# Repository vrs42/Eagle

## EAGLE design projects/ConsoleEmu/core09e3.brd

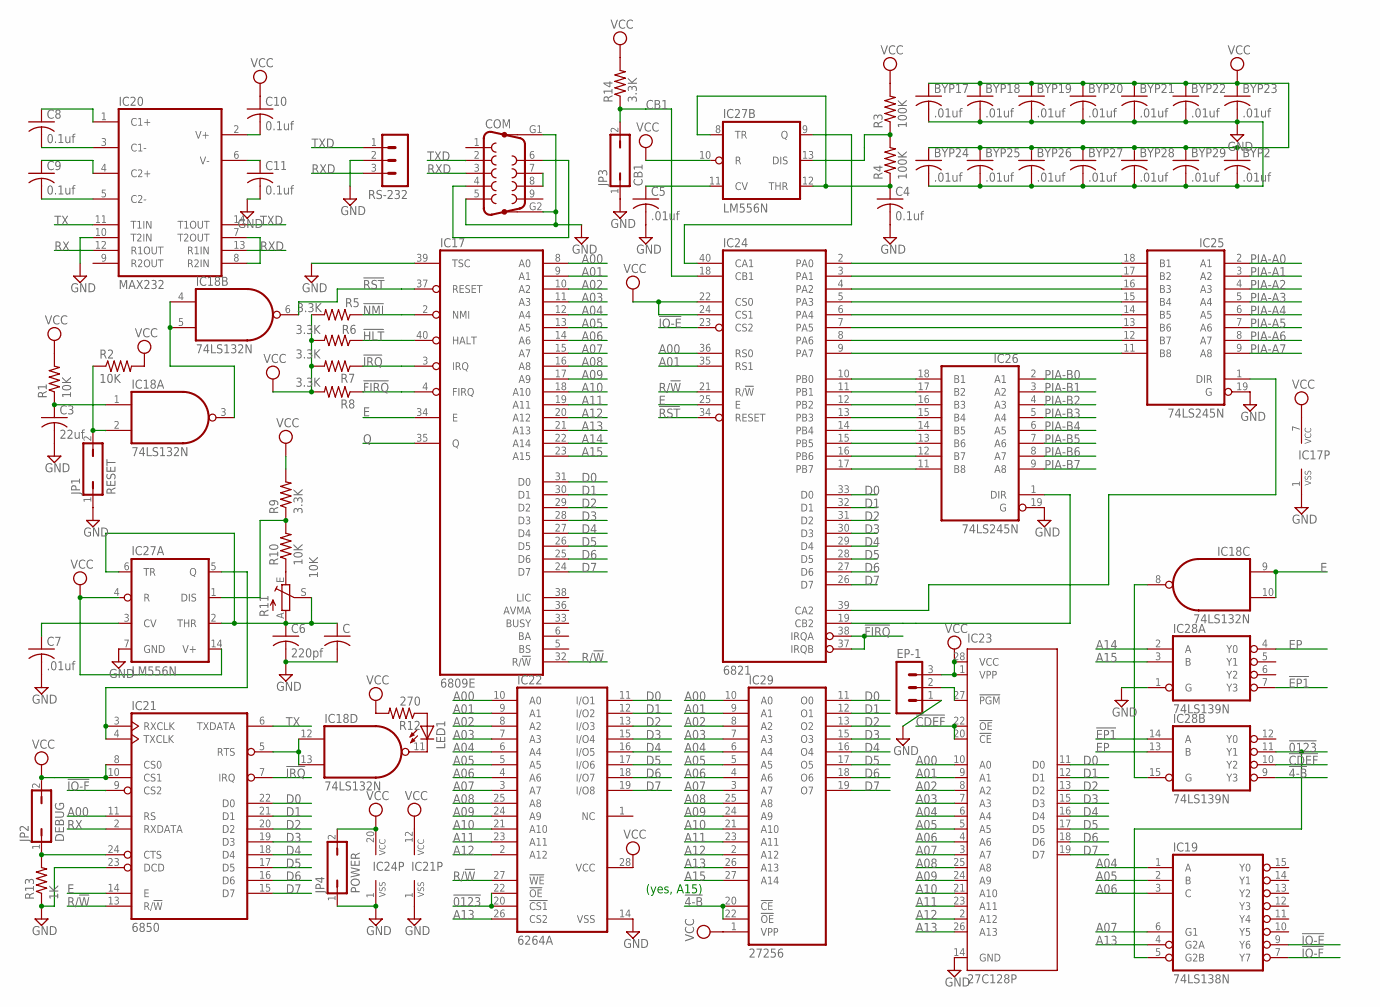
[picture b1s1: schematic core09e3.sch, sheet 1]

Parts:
BYP2, BYP17, BYP18, BYP19, BYP20, BYP21, BYP22, BYP23, BYP24, BYP25, BYP26, BYP27, BYP28, BYP29: .01uf; C050-025X075
C: C-US050-025X075; C050-025X075
C3: 22uf; C102-054X133
C4, C8, C9, C10, C11: 0.1uf; C050-025X075
C5, C7: .01uf; C050-025X075
C6: 220pf; C050-025X075
COM: F09HP
EP-1: MA03-1
IC17: 6809E; DIL40
IC18: 74LS132N; DIL14
IC19: 74LS138N; DIL16
IC20: MAX232; DIL16
IC21: 6850; DIL24
IC22: 6264A; DIL28-6
IC23: 27C128P; DIL28-6
IC24: 6821; DIL40
IC25, IC26: 74LS245N; DIL20
IC27: LM556N; DIL14
IC28: 74LS139N; DIL16
IC29: 27256; DIL28
JP1: RESET; JP1
JP2: DEBUG; JP1
JP3: CB1; JP1
JP4: POWER; JP1
LED1: LED3MM
R1, R2, R10: 10K; 0207/7
R3, R4: 100K; 0207/7
R5, R6, R7, R8, R9, R14: 3.3K; 0207/7
R11: 10K; SP19L
R12: 270; 0207/7
R13: 1K; 0207/7
RS-232: MA03-1

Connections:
!4-B: IC28.9 (Y3), IC29.20 (!CE), IC29.22 (!OE)
!0123: IC19.5 (G2B), IC22.20 (!CS1), IC22.22 (!OE), IC28.11 (Y1)
!CDEF: IC23.20 (!CE), IC23.22 (!OE), IC28.10 (Y2)
!EP1: IC28.7 (Y3), IC28.14 (A)
!FIRQ: IC17.4 (FIRQ), IC24.37 (IRQB), IC24.38 (IRQA), R8.1
!HLT: IC17.40 (HALT), R5.1
!IO-E: IC19.9 (Y6), IC24.23 (CS2)
!IO-F: IC19.7 (Y7), IC21.9 (CS2)
!IRQ: IC17.3 (IRQ), IC21.7 (IRQ), R7.1
!NMI: IC17.2 (NMI), R6.1
!RST: IC17.37 (RESET), IC18.6 (O), IC24.34 (RESET)
A00: IC17.8 (A0), IC21.11 (RS), IC22.10 (A0), IC23.10 (A0), IC24.36 (RS0), IC29.10 (A0)
A01: IC17.9 (A1), IC22.9 (A1), IC23.9 (A1), IC24.35 (RS1), IC29.9 (A1)
A02: IC17.10 (A2), IC22.8 (A2), IC23.8 (A2), IC29.8 (A2)
A03: IC17.11 (A3), IC22.7 (A3), IC23.7 (A3), IC29.7 (A3)
A04: IC17.12 (A4), IC19.1 (A), IC22.6 (A4), IC23.6 (A4), IC29.6 (A4)
A05: IC17.13 (A5), IC19.2 (B), IC22.5 (A5), IC23.5 (A5), IC29.5 (A5)
A06: IC17.14 (A6), IC19.3 (C), IC22.4 (A6), IC23.4 (A6), IC29.4 (A6)
A07: IC17.15 (A7), IC19.6 (G1), IC22.3 (A7), IC23.3 (A7), IC29.3 (A7)
A08: IC17.16 (A8), IC22.25 (A8), IC23.25 (A8), IC29.25 (A8)
A09: IC17.17 (A9), IC22.24 (A9), IC23.24 (A9), IC29.24 (A9)
A10: IC17.18 (A10), IC22.21 (A10), IC23.21 (A10), IC29.21 (A10)
A11: IC17.19 (A11), IC22.23 (A11), IC23.23 (A11), IC29.23 (A11)
A12: IC17.20 (A12), IC22.2 (A12), IC23.2 (A12), IC29.2 (A12)
A13: IC17.21 (A13), IC19.4 (G2A), IC22.26 (CS2), IC23.26 (A13), IC29.26 (A13)
A14: IC17.22 (A14), IC28.2 (A)
A15: IC17.23 (A15), IC28.3 (B), IC29.27 (A14)
CB1: IC24.18 (CB1), JP3.2, R14.1
D0: IC17.31 (D0), IC21.22 (D0), IC22.11 (I/O1), IC23.11 (D0), IC24.33 (D0), IC29.11 (O0)
D1: IC17.30 (D1), IC21.21 (D1), IC22.12 (I/O2), IC23.12 (D1), IC24.32 (D1), IC29.12 (O1)
D2: IC17.29 (D2), IC21.20 (D2), IC22.13 (I/O3), IC23.13 (D2), IC24.31 (D2), IC29.13 (O2)
D3: IC17.28 (D3), IC21.19 (D3), IC22.15 (I/O4), IC23.15 (D3), IC24.30 (D3), IC29.15 (O3)
D4: IC17.27 (D4), IC21.18 (D4), IC22.16 (I/O5), IC23.16 (D4), IC24.29 (D4), IC29.16 (O4)
D5: IC17.26 (D5), IC21.17 (D5), IC22.17 (I/O6), IC23.17 (D5), IC24.28 (D5), IC29.17 (O5)
D6: IC17.25 (D6), IC21.16 (D6), IC22.18 (I/O7), IC23.18 (D6), IC24.27 (D6), IC29.18 (O6)
D7: IC17.24 (D7), IC21.15 (D7), IC22.19 (I/O8), IC23.19 (D7), IC24.26 (D7), IC29.19 (O7)
E: IC17.34 (E), IC18.9 (I0), IC18.10 (I1), IC21.14 (E), IC24.25 (E); also elsewhere on the board
EP: IC28.4 (Y0), IC28.13 (B)
GND: BYP2.2, BYP17.2, BYP18.2, BYP19.2, BYP20.2, BYP21.2, BYP22.2, BYP23.2, BYP24.2, BYP25.2, BYP26.2, BYP27.2, BYP28.2, BYP29.2, C.2, C3.2, C4.2, C5.2, C6.2, C7.2, C11.2, COM.5, COM.G1, COM.G2, EP-1.1, IC17.1 (VSS), IC17.39 (TSC), IC18.7 (GND), IC19.8 (GND), IC20.10 (T2IN), IC20.15 (GND), IC21.1 (VSS), IC21.23 (DCD), IC22.14 (VSS), IC23.14 (GND), IC24.1 (VSS), IC25.10 (GND), IC25.19 (G), IC26.10 (GND), IC26.19 (G), IC27.7 (GND), IC28.1 (G), IC28.8 (GND), IC29.14 (GND), JP1.1, JP3.1, JP4.1, R13.1, RS-232.2; also elsewhere on the board
unnamed: COM.4, COM.6
unnamed: EP-1.2, IC23.27 (!PGM)
unnamed: IC24.2 (PA0), IC25.18 (B1)
unnamed: IC18.3 (O), IC18.4 (I0), IC18.5 (I1)
unnamed: C3.1, IC18.1 (I0), R1.1
unnamed: IC18.2 (I1), JP1.2, R2.1
unnamed: IC21.3 (RXCLK), IC21.4 (TXCLK), IC27.5 (Q)
unnamed: IC24.10 (PB0), IC26.18 (B1)
unnamed: IC24.11 (PB1), IC26.17 (B2)
unnamed: C.1, C6.1, IC27.2 (THR), IC27.6 (TR), R11.A, R11.S
unnamed: IC27.1 (DIS), R9.1, R10.2
unnamed: IC24.12 (PB2), IC26.16 (B3)
unnamed: IC24.13 (PB3), IC26.15 (B4)
unnamed: IC24.14 (PB4), IC26.14 (B5)
unnamed: IC24.15 (PB5), IC26.13 (B6)
unnamed: IC24.16 (PB6), IC26.12 (B7)
unnamed: IC24.17 (PB7), IC26.11 (B8)
unnamed: IC24.3 (PA1), IC25.17 (B2)
unnamed: IC24.4 (PA2), IC25.16 (B3)
unnamed: IC24.5 (PA3), IC25.15 (B4)
unnamed: IC24.6 (PA4), IC25.14 (B5)
unnamed: IC24.7 (PA5), IC25.13 (B6)
unnamed: IC24.8 (PA6), IC25.12 (B7)
unnamed: IC24.9 (PA7), IC25.11 (B8)
unnamed: IC24.19 (CB2), IC26.1 (DIR)
unnamed: IC24.39 (CA2), IC25.1 (DIR)
unnamed: IC24.40 (CA1), IC27.9 (Q)
unnamed: C4.1, IC27.8 (TR), IC27.12 (THR), R4.1
unnamed: IC27.13 (DIS), R3.1, R4.2
unnamed: C5.1, IC27.11 (CV)
unnamed: R10.1, R11.E
unnamed: COM.7, COM.8
unnamed: IC18.12 (I0), IC18.13 (I1), IC21.5 (RTS)
unnamed: IC18.11 (O), LED1.K (C)
unnamed: LED1.A, R12.1
unnamed: IC21.24 (CTS), JP2.1, R13.2
unnamed: IC18.8 (O), IC28.15 (G)
unnamed: IC20.7 (T2OUT), IC20.8 (R2IN)
unnamed: C7.1, IC27.3 (CV)
unnamed: C9.2, IC20.5 (C2-)
unnamed: C9.1, IC20.4 (C2+)
unnamed: C8.2, IC20.3 (C1-)
unnamed: C8.1, IC20.1 (C1+)
unnamed: C11.1, IC20.6 (V-)
unnamed: C10.2, IC20.2 (V+)
PIA-A0: IC25.2 (A1); also elsewhere on the board
PIA-A1: IC25.3 (A2); also elsewhere on the board
PIA-A2: IC25.4 (A3); also elsewhere on the board
PIA-A3: IC25.5 (A4); also elsewhere on the board
PIA-A4: IC25.6 (A5); also elsewhere on the board
PIA-A5: IC25.7 (A6); also elsewhere on the board
PIA-A6: IC25.8 (A7); also elsewhere on the board
PIA-A7: IC25.9 (A8); also elsewhere on the board
PIA-B0: IC26.2 (A1); also elsewhere on the board
PIA-B1: IC26.3 (A2); also elsewhere on the board
PIA-B2: IC26.4 (A3); also elsewhere on the board
PIA-B3: IC26.5 (A4); also elsewhere on the board
PIA-B4: IC26.6 (A5); also elsewhere on the board
PIA-B5: IC26.7 (A6); also elsewhere on the board
PIA-B6: IC26.8 (A7); also elsewhere on the board
PIA-B7: IC26.9 (A8); also elsewhere on the board
Q: IC17.35 (Q); also elsewhere on the board
R/!W: IC17.32 (R/!W), IC21.13 (R/!W), IC22.27 (!WE), IC24.21 (R/!W)
RX: IC20.12 (R1OUT), IC21.2 (RXDATA)
RXD: COM.3, IC20.13 (R1IN), RS-232.3
TX: IC20.11 (T1IN), IC21.6 (TXDATA)
TXD: COM.2, IC20.14 (T1OUT), RS-232.1
VCC: BYP2.1, BYP17.1, BYP18.1, BYP19.1, BYP20.1, BYP21.1, BYP22.1, BYP23.1, BYP24.1, BYP25.1, BYP26.1, BYP27.1, BYP28.1, BYP29.1, C10.1, EP-1.3, IC17.7 (VCC), IC18.14 (VCC), IC19.16 (VCC), IC20.16 (VCC), IC21.8 (CS0), IC21.10 (CS1), IC21.12 (VCC), IC22.28 (VCC), IC23.1 (VPP), IC23.28 (VCC), IC24.20 (VCC), IC24.22 (CS0), IC24.24 (CS1), IC25.20 (VCC), IC26.20 (VCC), IC27.4 (R), IC27.10 (R), IC27.14 (V+), IC28.16 (VCC), IC29.1 (VPP), IC29.28 (VCC), JP2.2, JP4.2, R1.2, R2.2, R3.2, R5.2, R6.2, R7.2, R8.2, R9.2, R12.2, R14.2; also elsewhere on the board

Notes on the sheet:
(yes, A15)

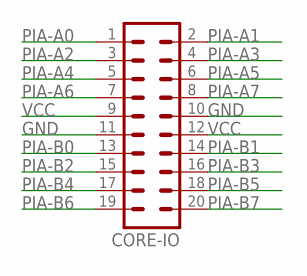
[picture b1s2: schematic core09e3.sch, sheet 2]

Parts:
CORE-IO: MA10-2

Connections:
GND: CORE-IO.10, CORE-IO.11; also elsewhere on the board
PIA-A0: CORE-IO.1; also elsewhere on the board
PIA-A1: CORE-IO.2; also elsewhere on the board
PIA-A2: CORE-IO.3; also elsewhere on the board
PIA-A3: CORE-IO.4; also elsewhere on the board
PIA-A4: CORE-IO.5; also elsewhere on the board
PIA-A5: CORE-IO.6; also elsewhere on the board
PIA-A6: CORE-IO.7; also elsewhere on the board
PIA-A7: CORE-IO.8; also elsewhere on the board
PIA-B0: CORE-IO.13; also elsewhere on the board
PIA-B1: CORE-IO.14; also elsewhere on the board
PIA-B2: CORE-IO.15; also elsewhere on the board
PIA-B3: CORE-IO.16; also elsewhere on the board
PIA-B4: CORE-IO.17; also elsewhere on the board
PIA-B5: CORE-IO.18; also elsewhere on the board
PIA-B6: CORE-IO.19; also elsewhere on the board
PIA-B7: CORE-IO.20; also elsewhere on the board
VCC: CORE-IO.9, CORE-IO.12; also elsewhere on the board

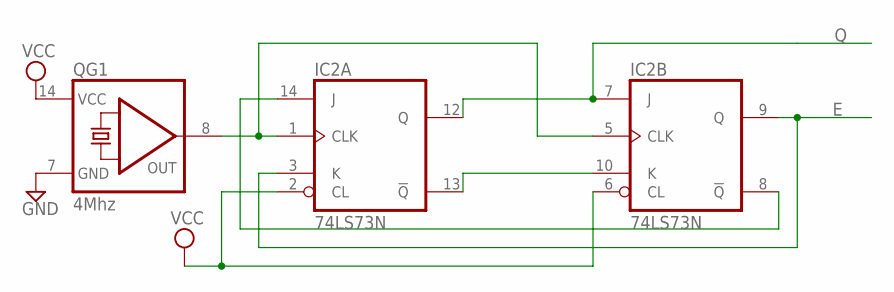
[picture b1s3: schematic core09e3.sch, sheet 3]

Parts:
IC2: 74LS73N; DIL14
QG1: 4Mhz; DIL14S

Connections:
E: IC2.3 (K), IC2.9 (Q); also elsewhere on the board
GND: IC2.11 (GND), QG1.7 (GND); also elsewhere on the board
unnamed: IC2.1 (CLK), IC2.5 (CLK), QG1.8 (OUT)
unnamed: IC2.10 (K), IC2.13 (!Q)
unnamed: IC2.8 (!Q), IC2.14 (J)
Q: IC2.7 (J), IC2.12 (Q); also elsewhere on the board
VCC: IC2.2 (CL), IC2.4 (VCC), IC2.6 (CL), QG1.14 (VCC); also elsewhere on the board

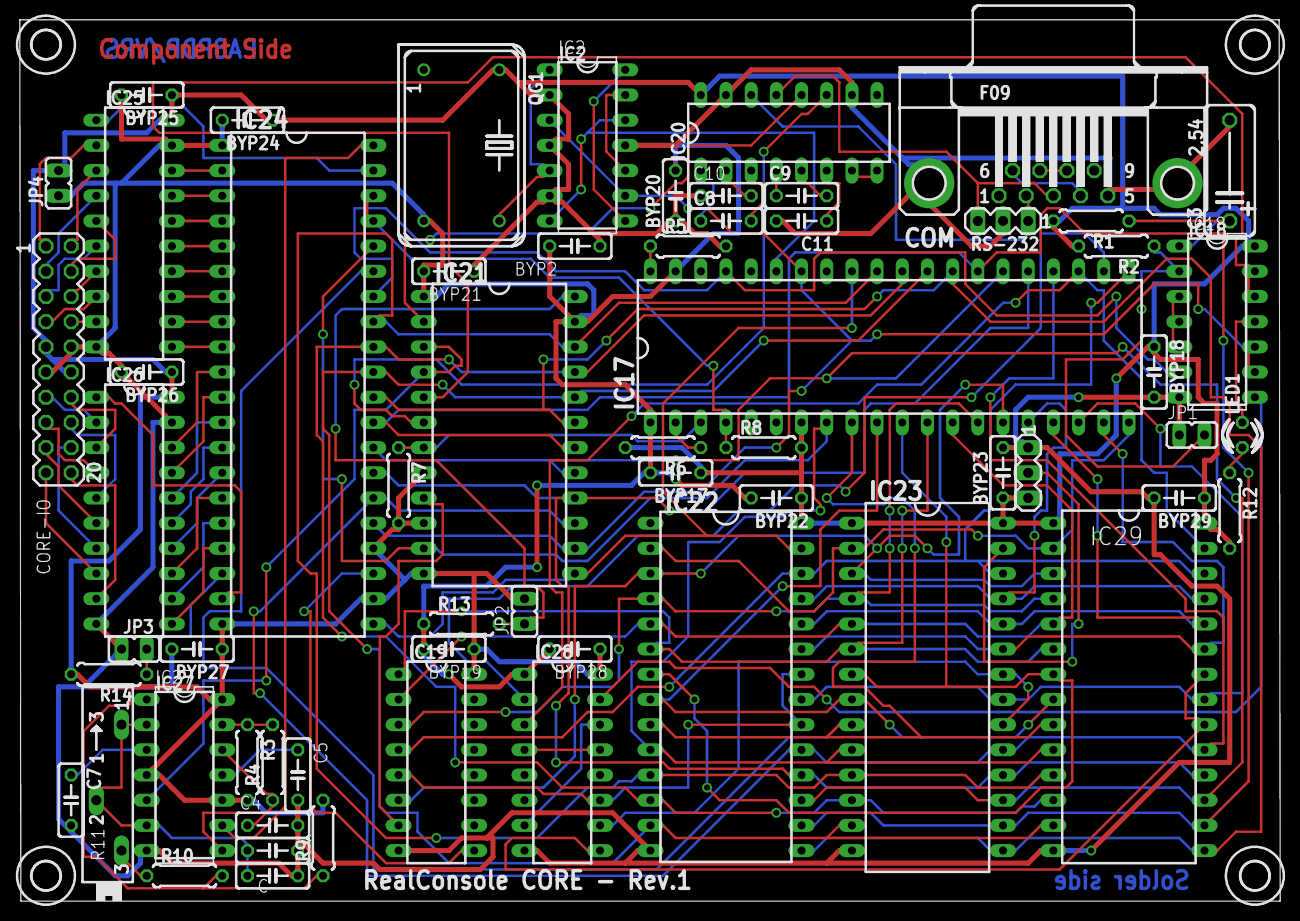
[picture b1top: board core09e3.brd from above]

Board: 2 copper layers, 127.1 x 88.9 mm, 66 parts (0 on the bottom side), 110 nets.

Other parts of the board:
U$3, U$4, U$5, U$6: 2,8

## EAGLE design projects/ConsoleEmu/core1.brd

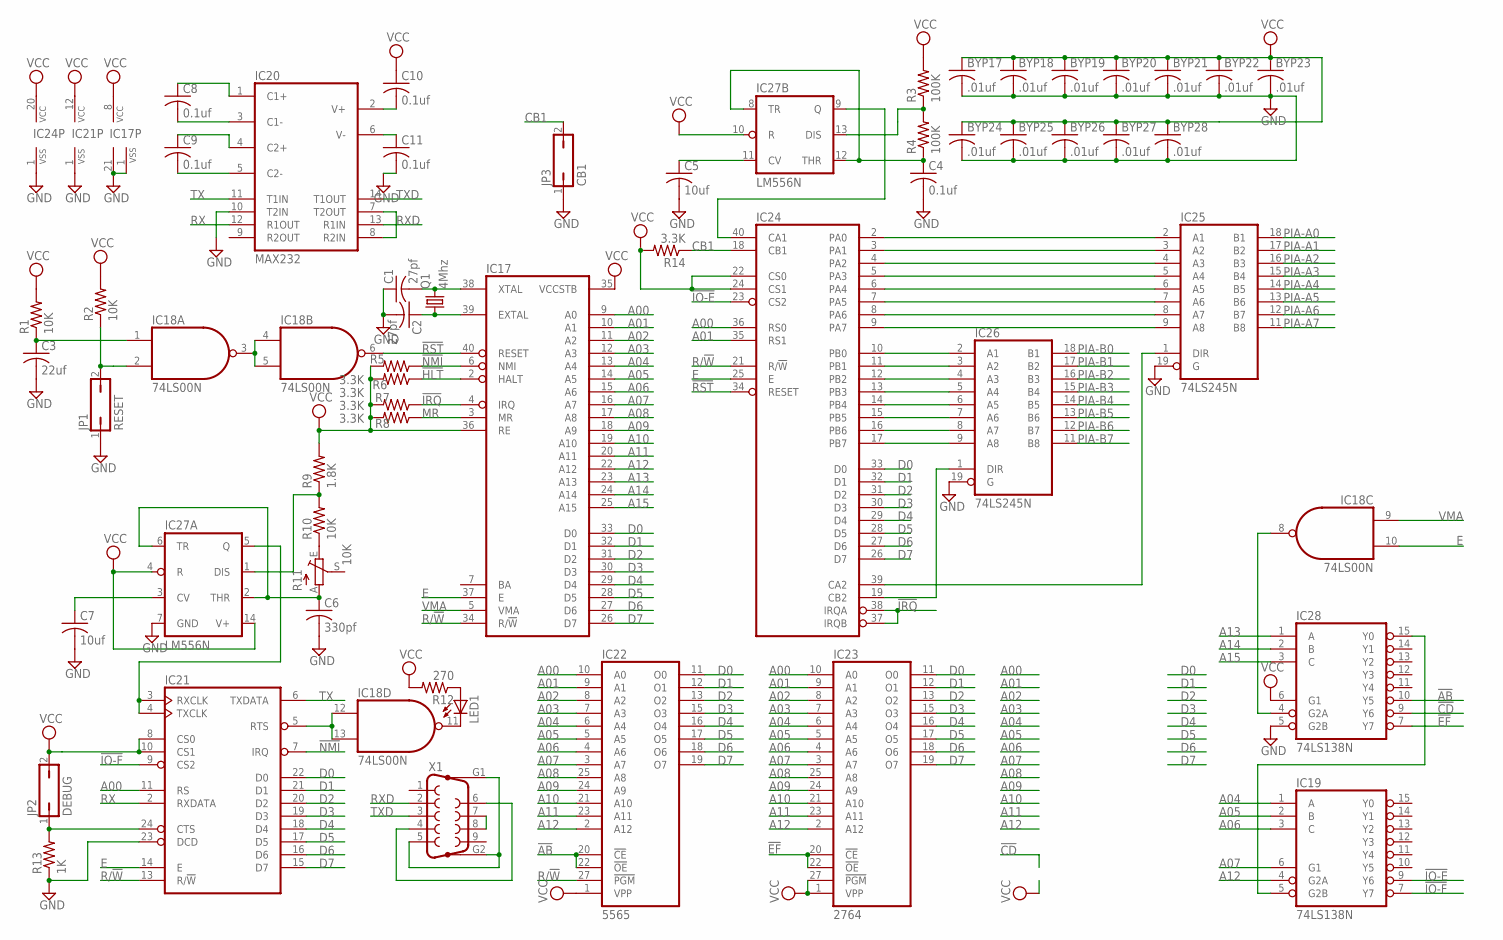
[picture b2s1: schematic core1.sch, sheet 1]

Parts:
BYP17, BYP18, BYP19, BYP20, BYP21, BYP22, BYP23, BYP24, BYP25, BYP26, BYP27, BYP28: .01uf; C050-025X075
C1, C2: 27pf; C050-025X075
C3: 22uf; C102-043X133
C4, C8, C9, C10, C11: 0.1uf; C050-025X075
C5, C7: 10uf; C050-025X075
C6: 330pf; C050-025X075
IC17: 6802; DIL40
IC18: 74LS00N; DIL14
IC19, IC28: 74LS138N; DIL16
IC20: MAX232; DIL16
IC21: 6850; DIL24
IC22: 5565; DIL28
IC23: 2764; DIL28
IC24: 6821; DIL40
IC25, IC26: 74LS245N; DIL20
IC27: LM556N; DIL14
JP1: RESET; JP1
JP2: DEBUG; JP1
JP3: CB1; JP1
LED1: LED3MM
Q1: 4Mhz; HC18U-V
R1, R2, R10: 10K; 0207/7
R3, R4: 100K; 0207/7
R5, R6, R7, R8, R14: 3.3K; 0207/7
R9: 1.8K; 0207/7
R11: 10K; SP19L
R12: 270; 0207/7
R13: 1K; 0207/7
X1: F09HP

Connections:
!AB: IC22.20 (!CE), IC22.22 (!OE), IC28.10 (Y5)
!CD: IC28.9 (Y6)
!EF: IC23.20 (!CE), IC23.22 (!OE), IC28.7 (Y7)
!HLT: IC17.2 (HALT), R5.1
!IO-E: IC19.9 (Y6), IC24.23 (CS2)
!IO-F: IC19.7 (Y7), IC21.9 (CS2)
!IRQ: IC17.4 (IRQ), IC24.37 (IRQB), IC24.38 (IRQA), R7.1
!NMI: IC17.6 (NMI), IC21.7 (IRQ), R6.1
!RST: IC17.40 (RESET), IC18.6 (O), IC24.34 (RESET)
A00: IC17.9 (A0), IC21.11 (RS), IC22.10 (A0), IC23.10 (A0), IC24.36 (RS0)
A01: IC17.10 (A1), IC22.9 (A1), IC23.9 (A1), IC24.35 (RS1)
A02: IC17.11 (A2), IC22.8 (A2), IC23.8 (A2)
A03: IC17.12 (A3), IC22.7 (A3), IC23.7 (A3)
A04: IC17.13 (A4), IC19.1 (A), IC22.6 (A4), IC23.6 (A4)
A05: IC17.14 (A5), IC19.2 (B), IC22.5 (A5), IC23.5 (A5)
A06: IC17.15 (A6), IC19.3 (C), IC22.4 (A6), IC23.4 (A6)
A07: IC17.16 (A7), IC19.6 (G1), IC22.3 (A7), IC23.3 (A7)
A08: IC17.17 (A8), IC22.25 (A8), IC23.25 (A8)
A09: IC17.18 (A9), IC22.24 (A9), IC23.24 (A9)
A10: IC17.19 (A10), IC22.21 (A10), IC23.21 (A10)
A11: IC17.20 (A11), IC22.23 (A11), IC23.23 (A11)
A12: IC17.22 (A12), IC19.4 (G2A), IC22.2 (A12), IC23.2 (A12)
A13: IC17.23 (A13), IC28.1 (A)
A14: IC17.24 (A14), IC28.2 (B)
A15: IC17.25 (A15), IC28.3 (C)
CB1: IC24.18 (CB1), JP3.2, R14.1
D0: IC17.33 (D0), IC21.22 (D0), IC22.11 (O0), IC23.11 (O0), IC24.33 (D0)
D1: IC17.32 (D1), IC21.21 (D1), IC22.12 (O1), IC23.12 (O1), IC24.32 (D1)
D2: IC17.31 (D2), IC21.20 (D2), IC22.13 (O2), IC23.13 (O2), IC24.31 (D2)
D3: IC17.30 (D3), IC21.19 (D3), IC22.15 (O3), IC23.15 (O3), IC24.30 (D3)
D4: IC17.29 (D4), IC21.18 (D4), IC22.16 (O4), IC23.16 (O4), IC24.29 (D4)
D5: IC17.28 (D5), IC21.17 (D5), IC22.17 (O5), IC23.17 (O5), IC24.28 (D5)
D6: IC17.27 (D6), IC21.16 (D6), IC22.18 (O6), IC23.18 (O6), IC24.27 (D6)
D7: IC17.26 (D7), IC21.15 (D7), IC22.19 (O7), IC23.19 (O7), IC24.26 (D7)
E: IC17.37 (E), IC18.10 (I1), IC21.14 (E), IC24.25 (E)
GND: BYP17.2, BYP18.2, BYP19.2, BYP20.2, BYP21.2, BYP22.2, BYP23.2, BYP24.2, BYP25.2, BYP26.2, BYP27.2, BYP28.2, C1.1, C2.2, C3.2, C4.2, C5.2, C6.2, C7.2, C11.2, IC17.1 (VSS), IC17.21 (VSS), IC18.7 (GND), IC19.8 (GND), IC20.10 (T2IN), IC20.15 (GND), IC21.1 (VSS), IC21.23 (DCD), IC22.14 (GND), IC23.14 (GND), IC24.1 (VSS), IC25.10 (GND), IC25.19 (G), IC26.10 (GND), IC26.19 (G), IC27.7 (GND), IC28.5 (G2B), IC28.8 (GND), JP1.1, JP3.1, R13.1; also elsewhere on the board
MR: IC17.3 (MR), R8.1
unnamed: C2.1, IC17.39 (EXTAL), Q1.1
unnamed: C1.2, IC17.38 (XTAL), Q1.2
unnamed: IC24.2 (PA0), IC25.2 (A1)
unnamed: IC18.3 (O), IC18.4 (I0), IC18.5 (I1)
unnamed: C3.1, IC18.1 (I0), R1.1
unnamed: IC18.2 (I1), JP1.2, R2.1
unnamed: IC21.3 (RXCLK), IC21.4 (TXCLK), IC27.5 (Q)
unnamed: IC24.10 (PB0), IC26.2 (A1)
unnamed: IC24.11 (PB1), IC26.3 (A2)
unnamed: C6.1, IC27.2 (THR), IC27.6 (TR), R11.A
unnamed: IC27.1 (DIS), R9.1, R10.2
unnamed: IC24.12 (PB2), IC26.4 (A3)
unnamed: IC24.13 (PB3), IC26.5 (A4)
unnamed: IC24.14 (PB4), IC26.6 (A5)
unnamed: IC24.15 (PB5), IC26.7 (A6)
unnamed: IC24.16 (PB6), IC26.8 (A7)
unnamed: IC24.17 (PB7), IC26.9 (A8)
unnamed: IC24.3 (PA1), IC25.3 (A2)
unnamed: IC24.4 (PA2), IC25.4 (A3)
unnamed: IC24.5 (PA3), IC25.5 (A4)
unnamed: IC24.6 (PA4), IC25.6 (A5)
unnamed: IC24.7 (PA5), IC25.7 (A6)
unnamed: IC24.8 (PA6), IC25.8 (A7)
unnamed: IC24.9 (PA7), IC25.9 (A8)
unnamed: IC24.19 (CB2), IC26.1 (DIR)
unnamed: IC24.39 (CA2), IC25.1 (DIR)
unnamed: IC24.40 (CA1), IC27.9 (Q)
unnamed: C4.1, IC27.8 (TR), IC27.12 (THR), R4.1
unnamed: IC27.13 (DIS), R3.1, R4.2
unnamed: C5.1, IC27.11 (CV)
unnamed: R10.1, R11.E
unnamed: X1.4, X1.6
unnamed: X1.7, X1.8
unnamed: X1.5, X1.G1, X1.G2
unnamed: IC18.12 (I0), IC18.13 (I1), IC21.5 (RTS)
unnamed: IC18.11 (O), LED1.K (C)
unnamed: LED1.A, R12.1
unnamed: IC21.24 (CTS), JP2.1, R13.2
unnamed: IC18.8 (O), IC28.4 (G2A)
unnamed: IC19.5 (G2B), IC28.15 (Y0)
unnamed: IC20.7 (T2OUT), IC20.8 (R2IN)
unnamed: C7.1, IC27.3 (CV)
unnamed: C9.2, IC20.5 (C2-)
unnamed: C9.1, IC20.4 (C2+)
unnamed: C8.2, IC20.3 (C1-)
unnamed: C8.1, IC20.1 (C1+)
unnamed: C11.1, IC20.6 (V-)
unnamed: C10.2, IC20.2 (V+)
PIA-A0: IC25.18 (B1); also elsewhere on the board
PIA-A1: IC25.17 (B2); also elsewhere on the board
PIA-A2: IC25.16 (B3); also elsewhere on the board
PIA-A3: IC25.15 (B4); also elsewhere on the board
PIA-A4: IC25.14 (B5); also elsewhere on the board
PIA-A5: IC25.13 (B6); also elsewhere on the board
PIA-A6: IC25.12 (B7); also elsewhere on the board
PIA-A7: IC25.11 (B8); also elsewhere on the board
PIA-B0: IC26.18 (B1); also elsewhere on the board
PIA-B1: IC26.17 (B2); also elsewhere on the board
PIA-B2: IC26.16 (B3); also elsewhere on the board
PIA-B3: IC26.15 (B4); also elsewhere on the board
PIA-B4: IC26.14 (B5); also elsewhere on the board
PIA-B5: IC26.13 (B6); also elsewhere on the board
PIA-B6: IC26.12 (B7); also elsewhere on the board
PIA-B7: IC26.11 (B8); also elsewhere on the board
R/!W: IC17.34 (R/!W), IC21.13 (R/!W), IC22.27 (!PGM), IC24.21 (R/!W)
RX: IC20.12 (R1OUT), IC21.2 (RXDATA)
RXD: IC20.13 (R1IN), X1.2
TX: IC20.11 (T1IN), IC21.6 (TXDATA)
TXD: IC20.14 (T1OUT), X1.3
VCC: BYP17.1, BYP18.1, BYP19.1, BYP20.1, BYP21.1, BYP22.1, BYP23.1, BYP24.1, BYP25.1, BYP26.1, BYP27.1, BYP28.1, C10.1, IC17.8 (VCC), IC17.35 (VCCSTB), IC17.36 (RE), IC18.14 (VCC), IC19.16 (VCC), IC20.16 (VCC), IC21.8 (CS0), IC21.10 (CS1), IC21.12 (VCC), IC22.1 (VPP), IC22.28 (VCC), IC23.1 (VPP), IC23.27 (!PGM), IC23.28 (VCC), IC24.20 (VCC), IC24.22 (CS0), IC24.24 (CS1), IC25.20 (VCC), IC26.20 (VCC), IC27.4 (R), IC27.10 (R), IC27.14 (V+), IC28.6 (G1), IC28.16 (VCC), JP2.2, R1.2, R2.2, R3.2, R5.2, R6.2, R7.2, R8.2, R9.2, R12.2, R14.2; also elsewhere on the board
VMA: IC17.5 (VMA), IC18.9 (I0)

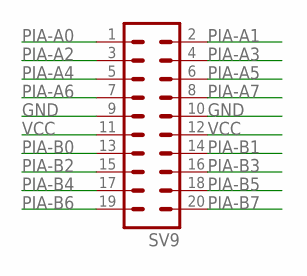
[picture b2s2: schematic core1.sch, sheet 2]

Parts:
SV9: MA10-2

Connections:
GND: SV9.9, SV9.10; also elsewhere on the board
PIA-A0: SV9.1; also elsewhere on the board
PIA-A1: SV9.2; also elsewhere on the board
PIA-A2: SV9.3; also elsewhere on the board
PIA-A3: SV9.4; also elsewhere on the board
PIA-A4: SV9.5; also elsewhere on the board
PIA-A5: SV9.6; also elsewhere on the board
PIA-A6: SV9.7; also elsewhere on the board
PIA-A7: SV9.8; also elsewhere on the board
PIA-B0: SV9.13; also elsewhere on the board
PIA-B1: SV9.14; also elsewhere on the board
PIA-B2: SV9.15; also elsewhere on the board
PIA-B3: SV9.16; also elsewhere on the board
PIA-B4: SV9.17; also elsewhere on the board
PIA-B5: SV9.18; also elsewhere on the board
PIA-B6: SV9.19; also elsewhere on the board
PIA-B7: SV9.20; also elsewhere on the board
VCC: SV9.11, SV9.12; also elsewhere on the board

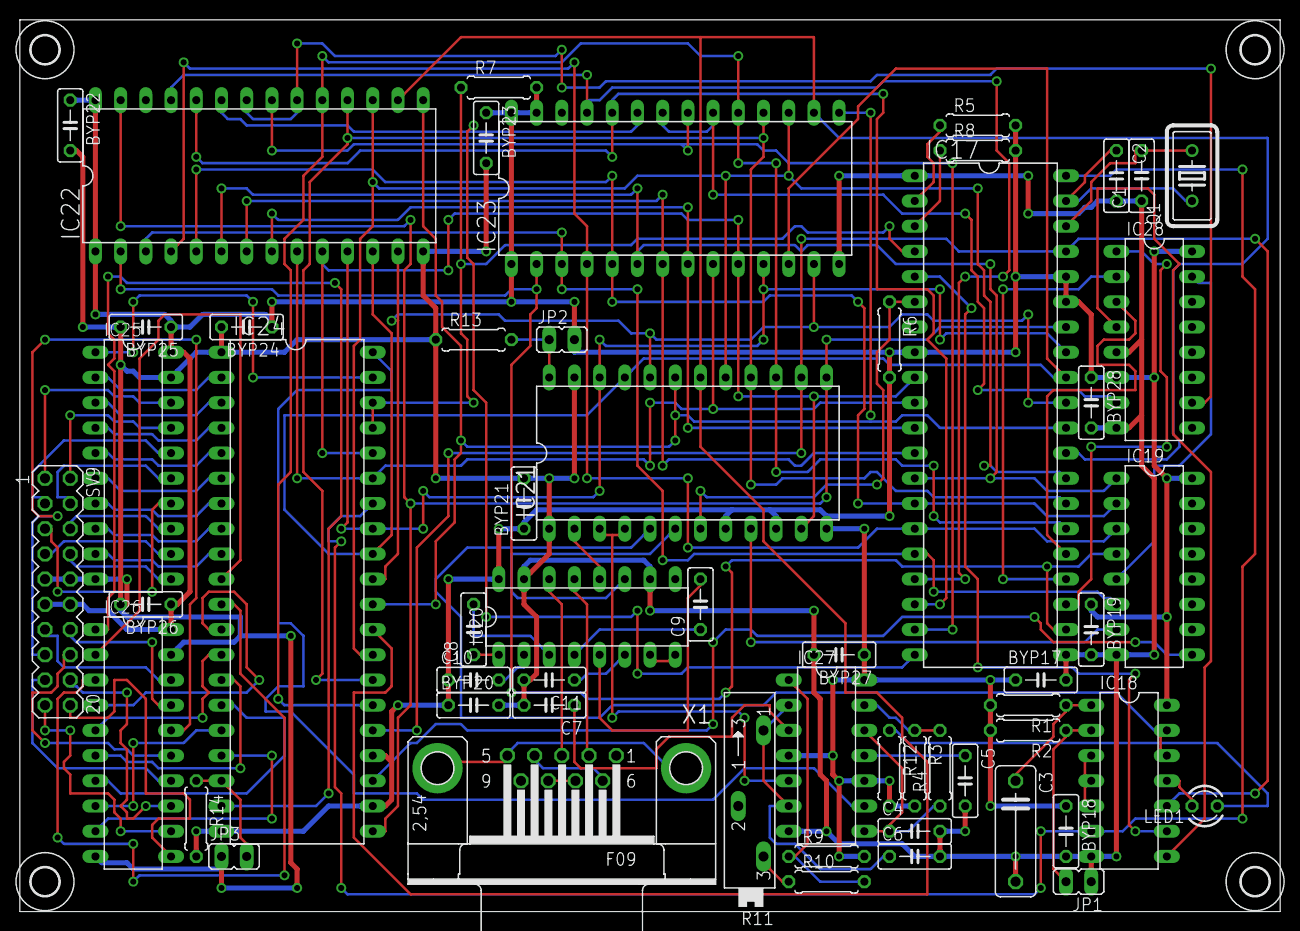
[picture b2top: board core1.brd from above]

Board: 2 copper layers, 127.0 x 89.8 mm, 60 parts (0 on the bottom side), 107 nets.

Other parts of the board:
U$3, U$4, U$5, U$6: 2,8
